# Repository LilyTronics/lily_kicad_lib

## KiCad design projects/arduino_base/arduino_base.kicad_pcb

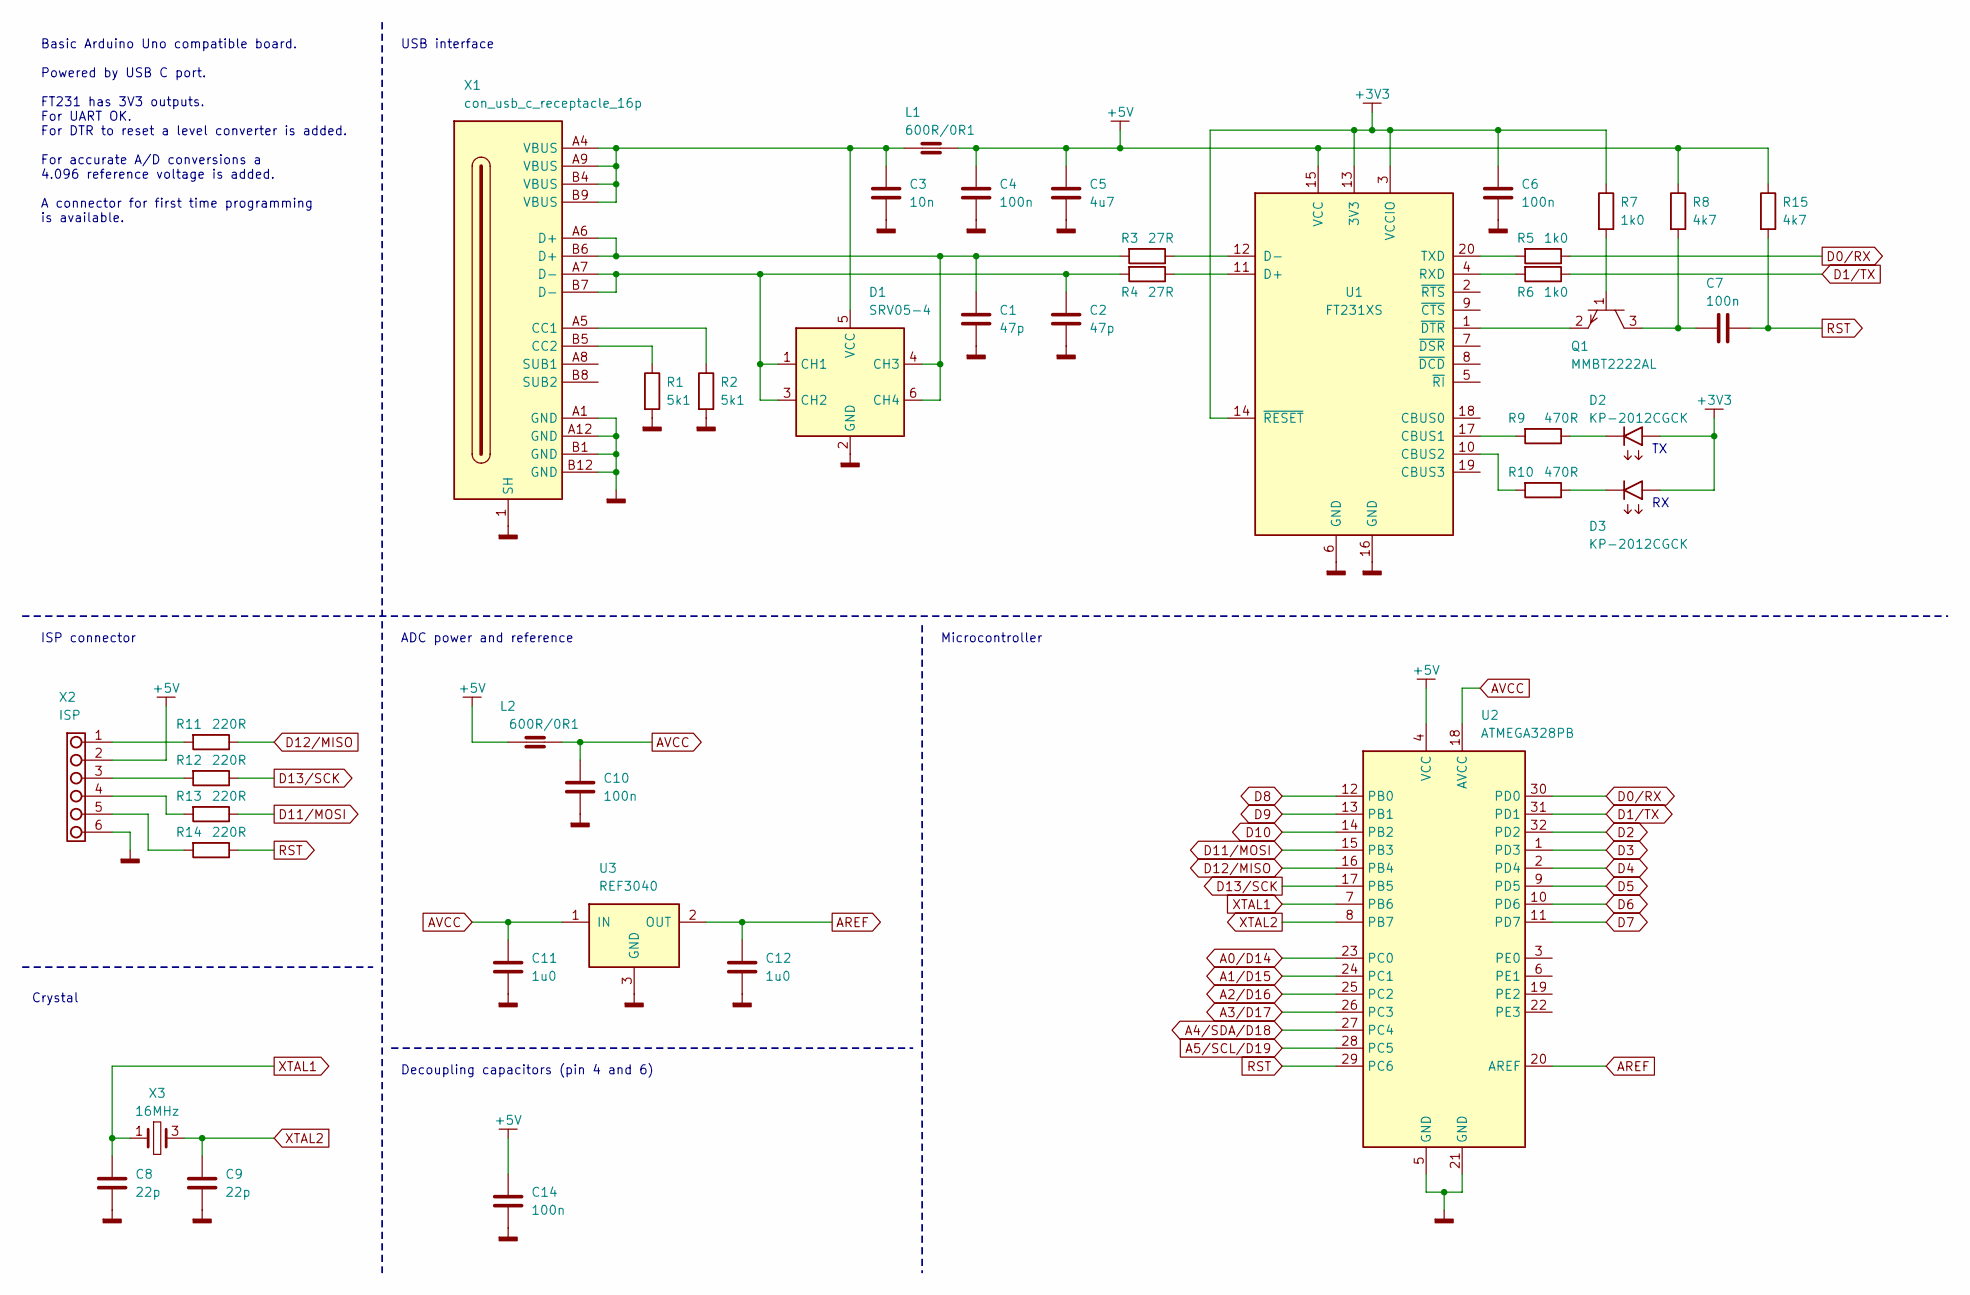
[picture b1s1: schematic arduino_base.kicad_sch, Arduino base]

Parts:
C1, C2: 47p; cap_0805; JLCPCB_ID C107118
C3: 10n; cap_0805; JLCPCB_ID C83170
C4, C6, C7, C10, C14: 100n; cap_0805; JLCPCB_ID C49678
C5: 4u7; cap_0805; JLCPCB_ID C1779
C8, C9: 22p; cap_0805; JLCPCB_ID C105623
C11, C12: 1u0; cap_0805; JLCPCB_ID C28323
D1: SRV05-4; sot23-6_sc74; JLCPCB_ID C1975211
D2, D3: KP-2012CGCK; led_0805; JLCPCB_ID C598271
L1, L2: 600R/0R1; ind_0805; JLCPCB_ID C21519
Q1: MMBT2222AL; sot23; JLCPCB_ID C82460
R1, R2: 5k1; res_0805; JLCPCB_ID C84375
R3, R4: 27R; res_0805; JLCPCB_ID C163408
R5, R6, R7: 1k0; res_0805; JLCPCB_ID C95781
R8, R15: 4k7; res_0805; JLCPCB_ID C60816
R9, R10: 470R; res_0805; JLCPCB_ID C114564
R11, R12, R13, R14: 220R; res_0805; JLCPCB_ID C114519
U1: FT231XS; ssop20_pitch25_341x154mil; JLCPCB_ID C132160
U2: ATMEGA328PB; tqfp32_pitch0.8_7x7mm; JLCPCB_ID C132230
U3: REF3040; sot23; JLCPCB_ID C19415
X1: con_usb_c_receptacle_16p; JLCPCB_ID C2765186
X2: ISP; con_header_2x03_2.54mm_th; JLCPCB_ID NO_ID
X3: 16MHz; crystal_3225; JLCPCB_ID C89371

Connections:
+3V3: C6.1, D2.2 (A), D3.2 (A), R7.1, U1.3 (VCCIO), U1.13 (3V3), U1.14 (~RESET)
+5V: C4.1, C5.1, C14.1, L1.2, L2.1, R8.1, R15.1, U1.15 (VCC), U2.4 (VCC), X2.2
A0/D14: U2.23 (PC0)
A1/D15: U2.24 (PC1)
A2/D16: U2.25 (PC2)
A3/D17: U2.26 (PC3)
A4/SDA/D18: U2.27 (PC4)
A5/SCL/D19: U2.28 (PC5)
AREF: C12.1, U2.20 (AREF), U3.2 (OUT)
AVCC: C10.1, C11.1, L2.2, U2.18 (AVCC), U3.1 (IN)
D0/RX: R5.1, U2.30 (PD0)
D1/TX: R6.1, U2.31 (PD1)
D2: U2.32 (PD2)
D3: U2.1 (PD3)
D4: U2.2 (PD4)
D5: U2.9 (PD5)
D6: U2.10 (PD6)
D7: U2.11 (PD7)
D8: U2.12 (PB0)
D9: U2.13 (PB1)
D10: U2.14 (PB2)
D11/MOSI: R13.1, U2.15 (PB3)
D12/MISO: R11.1, U2.16 (PB4)
D13/SCK: R12.1, U2.17 (PB5)
GND: C1.2, C2.2, C3.2, C4.2, C5.2, C6.2, C8.2, C9.2, C10.2, C11.2, C12.2, C14.2, D1.2 (GND), R1.2, R2.2, U1.6 (GND), U1.16 (GND), U2.5 (GND), U2.21 (GND), U3.3 (GND), X1.1 (SH), X1.A1 (GND), X1.A12 (GND), X1.B1 (GND), X1.B12 (GND), X2.6
unnamed: C7.2, Q1.3, R8.2
unnamed: C2.1, D1.1 (CH1), D1.3 (CH2), R4.2, X1.A7 (D-), X1.B7 (D-)
unnamed: C1.1, D1.4 (CH3), D1.6 (CH4), R3.2, X1.A6 (D+), X1.B6 (D+)
unnamed: C3.1, D1.5 (VCC), L1.1, X1.A4 (VBUS), X1.A9 (VBUS), X1.B4 (VBUS), X1.B9 (VBUS)
unnamed: D2.1 (K), R9.1
unnamed: D3.1 (K), R10.1
unnamed: Q1.1, R7.2
unnamed: R11.2, X2.1
unnamed: R12.2, X2.3
unnamed: R13.2, X2.4
unnamed: R14.2, X2.5
unnamed: R9.2, U1.17 (CBUS1)
unnamed: R10.2, U1.10 (CBUS2)
unnamed: R4.1, U1.11 (D+)
unnamed: R3.1, U1.12 (D-)
unnamed: R6.2, U1.4 (RXD)
unnamed: R5.2, U1.20 (TXD)
unnamed: Q1.2, U1.1 (~DTR)
unnamed: R2.1, X1.A5 (CC1)
unnamed: R1.1, X1.B5 (CC2)
RST: C7.1, R14.1, R15.2, U2.29 (PC6)
XTAL1: C8.1, U2.7 (PB6), X3.1
XTAL2: C9.1, U2.8 (PB7), X3.3

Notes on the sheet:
Basic Arduino Uno compatible board. Powered by USB C port. FT231 has 3V3 outputs. For UART OK. For DTR to reset a level converter is added. For accurate A/D conversions a 4.096 reference voltage is added. A connector for first time programming is available.
Crystal
USB interface
Decoupling capacitors (pin 4 and 6)
Microcontroller
ISP connector
ADC power and reference

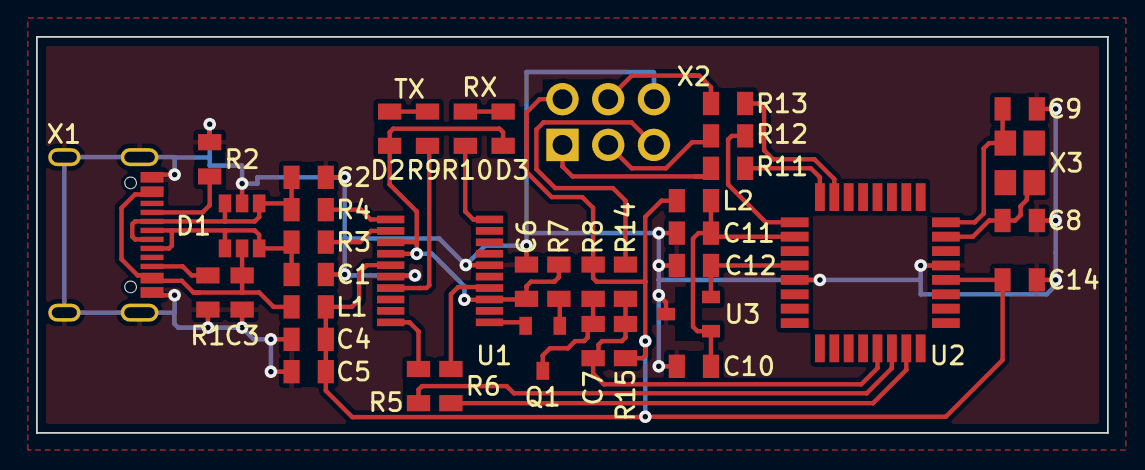
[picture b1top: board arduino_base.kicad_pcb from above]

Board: 2 copper layers, 59.5 x 22.0 mm, 40 parts (0 on the bottom side), 33 nets.

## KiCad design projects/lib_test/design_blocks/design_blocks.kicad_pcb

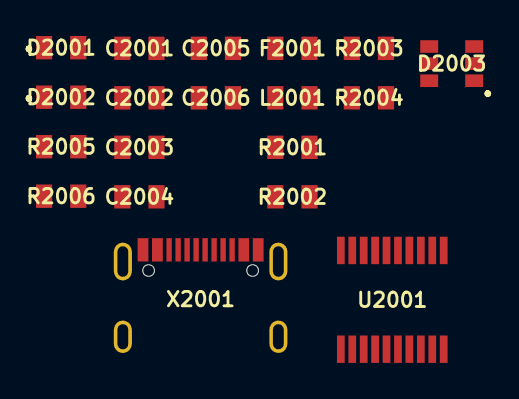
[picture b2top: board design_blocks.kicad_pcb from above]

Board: 2 copper layers, 19 parts (0 on the bottom side), 15 nets, no tracks yet.

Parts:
C2001: 10n; cap_0805
C2002, C2004: 100n; cap_0805
C2003: 4u7; cap_0805
C2005, C2006: 47p; cap_0805
D2001: RX; led_0805
D2002: TX; led_0805
D2003: SRV05-4; sot23-6_sc74
F2001: 0.35A/0.75A; fuse_ptc_0805
L2001: 600R/2A; ind_0805
R2001, R2002: 27R; res_0805
R2003, R2004: 5k1; res_0805
R2005, R2006: 470R; res_0805
U2001: FT231XS; ssop20_pitch25_341x154mil
X2001: usb_c; con_usb_c_receptacle_16p

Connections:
GND: C2001.2, C2002.2, C2003.2, C2004.2, C2005.2, C2006.2, D2003.2 (GND), R2003.2, R2004.2, U2001.6 (GND), U2001.16 (GND), X2001.1 (SH), X2001.A1 (GND), X2001.A12 (GND), X2001.B1 (GND), X2001.B12 (GND)
unnamed: C2004.1, D2001.2 (A), D2002.2 (A), U2001.3 (VCCIO), U2001.13 (3V3), U2001.14 (~RESET)
unnamed: D2001.1 (K), R2005.1
unnamed: D2002.1 (K), R2006.1
unnamed: C2006.1, D2003.1 (CH1), D2003.3 (CH2), R2002.2, X2001.A7 (D-), X2001.B7 (D-)
unnamed: C2005.1, D2003.4 (CH3), D2003.6 (CH4), R2001.2, X2001.A6 (D+), X2001.B6 (D+)
unnamed: C2001.1, D2003.5 (VCC), F2001.2, L2001.1
unnamed: F2001.1, X2001.A4 (VBUS), X2001.A9 (VBUS), X2001.B4 (VBUS), X2001.B9 (VBUS)
unnamed: R2005.2, U2001.17 (CBUS1)
unnamed: R2006.2, U2001.10 (CBUS2)
unnamed: R2001.1, U2001.11 (D+)
unnamed: R2002.1, U2001.12 (D-)
unnamed: C2002.1, C2003.1, L2001.2, U2001.15 (VCC)
unnamed: R2004.1, X2001.A5 (CC1)
unnamed: R2003.1, X2001.B5 (CC2)
